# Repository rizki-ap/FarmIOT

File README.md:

# FarmIOT
Hidroponic, Aquaponic automation system with IOT for TelkomUniversity Research

**Version-1

Using modules :
- PH-sensor of PH-4502C
- EC/TDS sensor 
- DHT-22 Air Temperature and Humidity Sensor
- GUVA-based UV sensor
- ESP32 module for wifi+BLE
- Arduino-Nano for sensor reading and control
- 5-pin 5v relays
- 7-24vdc power supply

IOT server method:

Data Uploading Query:
http://hydropoda.smartiotindo.com/tes2.php?key_api=HibahYPT2021&s0=0&s1=1&s2=2&s3=3&s4=4&s5=5

Data Uploading Respon:
{"id":"1","id_pengguna":"2","security_key":"xeWlBl%2F98qVUtyxiVAL2ArVyr0md2L%2Bdd0JXrzc5wIs%3D","gambar":"","date_time":"2020-12-17 09:36:02"}

Parameter Request Query:
http://hydropoda.smartiotindo.com/tes3.php?key_api=HibahYPT2021&jenis=Pakcoy or
http://hydropoda.smartiotindo.com/tes3.php?key_api=HibahYPT2021&jenis=Selada or
http://hydropoda.smartiotindo.com/tes3.php?key_api=HibahYPT2021&jenis=Bayam or
http://hydropoda.smartiotindo.com/tes3.php?key_api=HibahYPT2021&jenis=Kangkung or
http://hydropoda.smartiotindo.com/tes3.php?key_api=HibahYPT2021&jenis=Sawi

Parameter Request Respon:
{"ph_b":"5.5000","ph_a":"6.5000","ppm_b":"1050.0000","ppm_a":"1400.0000","suhu_b":"18.0000","suhu_a":"22.0000","kelembaban_b":"73.0000","kelembaban_a":"89.0000","rataan_cahaya":"12000.000","created_time":"2020-06-22 02:03:28"}

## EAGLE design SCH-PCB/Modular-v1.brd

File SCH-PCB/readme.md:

V1 modular design

Schematic

PCB

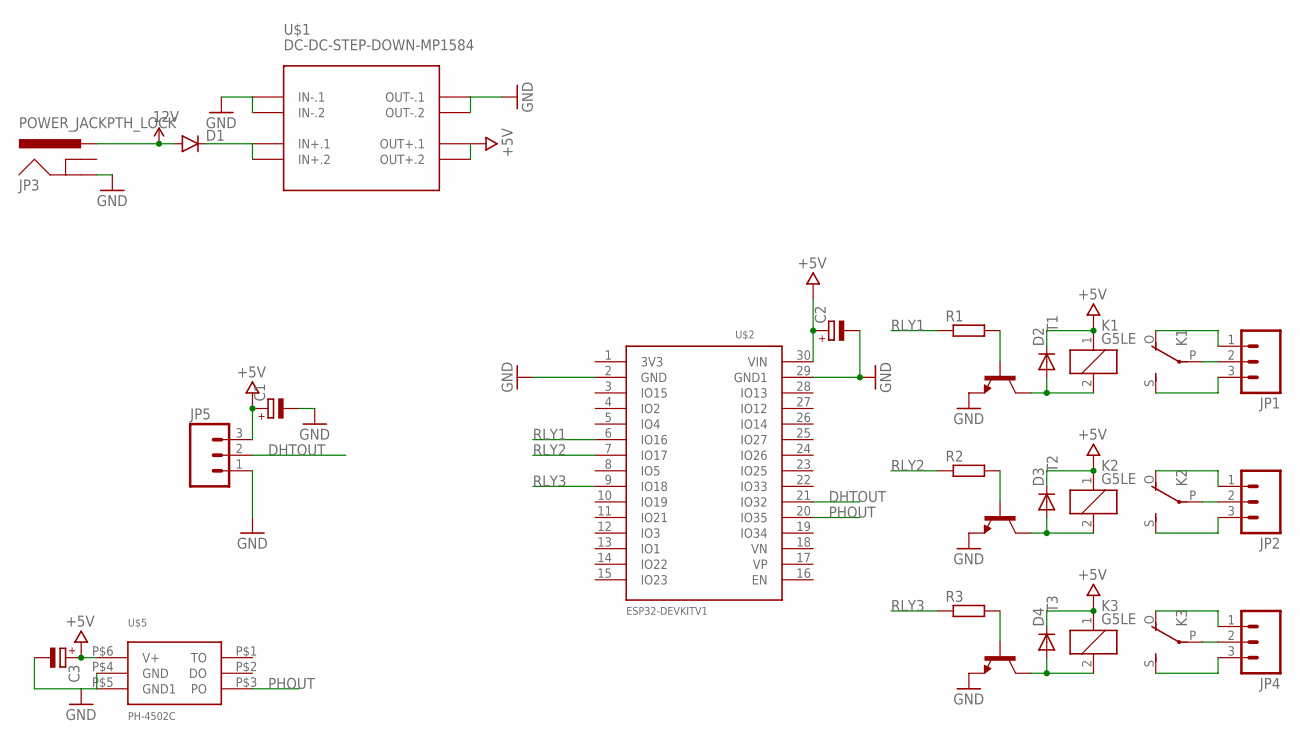
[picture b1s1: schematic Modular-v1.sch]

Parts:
C1: CPOL-EUE5-5; E5-5
C2: CPOL-EUE5-13; E5-13
C3: CPOL-EUE5-8.5; E5-8,5
D1: DIODEKIT; DIODE-1N4148-KIT
D2, D3, D4: DIODE-D-2.5; D-2.5
JP1, JP2, JP4, JP5: M03-SCREW-5MM; SCREWTERMINAL-5MM-3
JP3: POWER_JACKPTH_LOCK; POWER_JACK_PTH_LOCK
K1, K2, K3: G5LE
R1, R2, R3: R-EU_R0805; R0805
T1, T2, T3: -NPN-TO92-EBC; TO92-EBC
U$1: DC-DC-STEP-DOWN-MP1584
U$2: ESP32DEVKITV1; ESP32-DEVKITV1
U$5: PH-4502C

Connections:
12V: D1.A, JP3.PWR
+5V: C1.+, C2.+, C3.+, D2.C, D3.C, D4.C, JP5.3, K1.1, K2.1, K3.1, U$1.OUT+.1, U$1.OUT+.2, U$2.30 (VIN), U$5.P$6 (V+)
DHTOUT: JP5.2, U$2.21 (IO32)
GND: C1.-, C2.-, C3.-, JP3.GND, JP5.1, T1.E, T2.E, T3.E, U$1.IN-.1, U$1.IN-.2, U$1.OUT-.1, U$1.OUT-.2, U$2.2 (GND), U$2.29 (GND1), U$5.P$4 (GND), U$5.P$5 (GND1)
unnamed: D1.C, U$1.IN+.1, U$1.IN+.2
unnamed: JP1.2, K1.P
unnamed: JP2.2, K2.P
unnamed: JP4.2, K3.P
unnamed: D2.A, K1.2, T1.C
unnamed: D3.A, K2.2, T2.C
unnamed: D4.A, K3.2, T3.C
unnamed: R1.2, T1.B
unnamed: R2.2, T2.B
unnamed: R3.2, T3.B
unnamed: JP1.1, K1.O
unnamed: JP1.3, K1.S
unnamed: JP2.1, K2.O
unnamed: JP2.3, K2.S
unnamed: JP4.1, K3.O
unnamed: JP4.3, K3.S
PHOUT: U$2.20 (IO35), U$5.P$3 (PO)
RLY1: R1.1, U$2.6 (IO16)
RLY2: R2.1, U$2.7 (IO17)
RLY3: R3.1, U$2.9 (IO18)

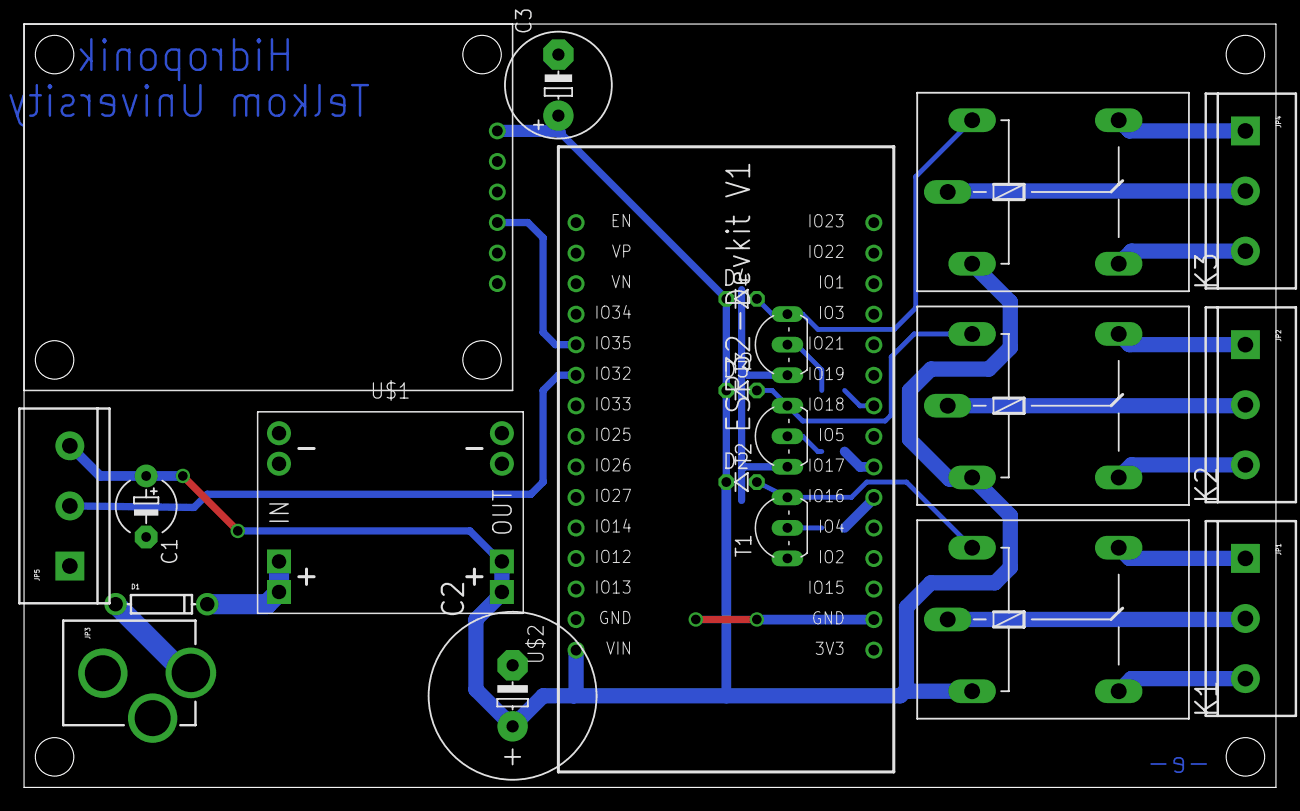
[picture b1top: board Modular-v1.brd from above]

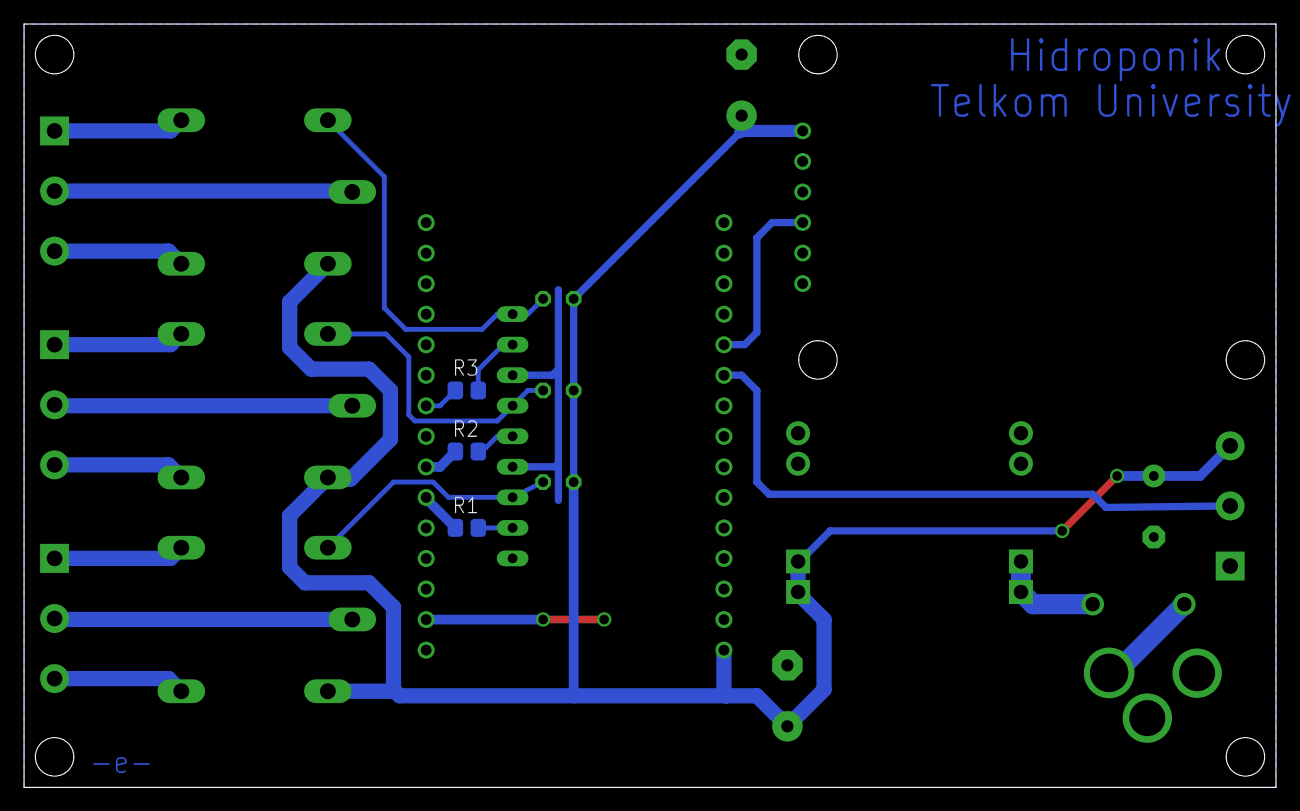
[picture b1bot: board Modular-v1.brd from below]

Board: 2 copper layers, 104.1 x 63.5 mm, 24 parts (3 on the bottom side), 24 nets.

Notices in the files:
parts and their libraries:
SparkFun-Connectors: Licensing: Creative Commons ShareAlike 4.0 International - https://creativecommons.org/licenses/by-sa/4.0
diy-modules-v180: Released under the Creative Commons Attribution 4.0 International License: http://creativecommons.org/licenses/by/4.0
